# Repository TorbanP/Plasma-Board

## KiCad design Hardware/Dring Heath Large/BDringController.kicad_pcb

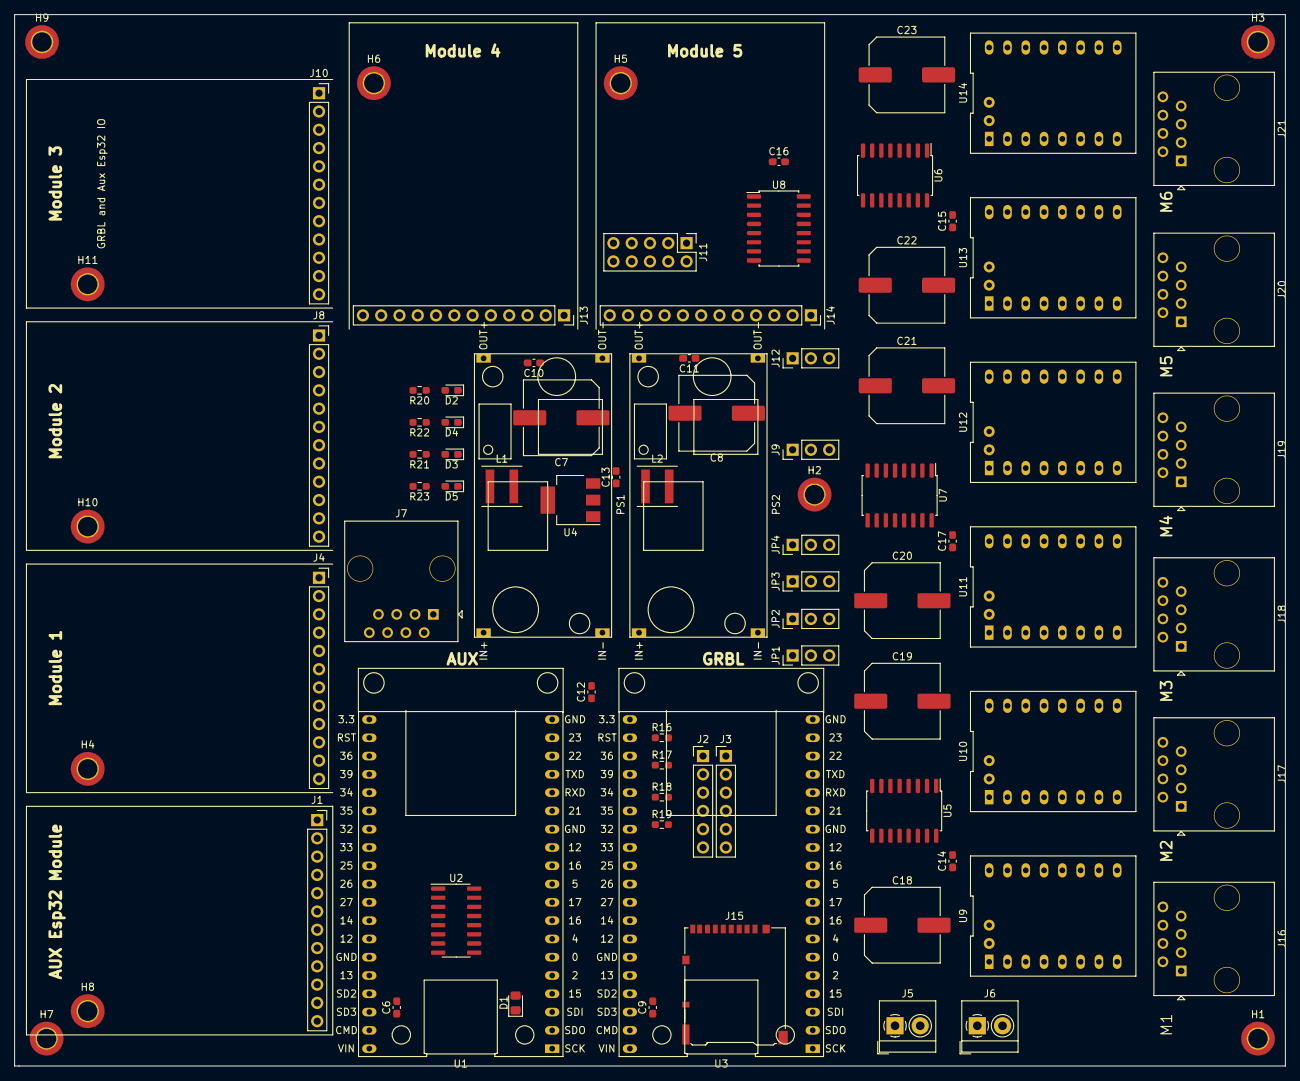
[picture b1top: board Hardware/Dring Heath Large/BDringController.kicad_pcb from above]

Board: 2 copper layers, 176.5 x 146.1 mm, 85 parts (0 on the bottom side), 127 nets, no tracks yet.

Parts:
C6, C9, C10, C11, C14, C15, C16, C17: 100nf; C_0603_1608Metric_Pad1.08x0.95mm_HandSolder
C7, C8, C18, C19, C20, C21, C22, C23: 330uf; C_Elec_10x10.2
C12, C13: 10uf; C_0603_1608Metric_Pad1.08x0.95mm_HandSolder
D1: B340A; D_0805_2012Metric_Pad1.15x1.40mm_HandSolder
D2: Vdrive; D_0603_1608Metric_Pad1.05x0.95mm_HandSolder
D3: 5v; D_0603_1608Metric_Pad1.05x0.95mm_HandSolder
D4: 15v; D_0603_1608Metric_Pad1.05x0.95mm_HandSolder
D5: 3.3v; D_0603_1608Metric_Pad1.05x0.95mm_HandSolder
H1, H2, H3, H4, H5, H6, H7, H8, H9, H10, H11: MountingHole_2.7mm_M2.5_DIN965_Pad_TopBottom
J1, J4: Module 1; PinSocket_1x12_P2.54mm_Vertical
J2: Jumper; PinHeader_1x06_P2.54mm_Vertical
J3: Motor; PinHeader_1x06_P2.54mm_Vertical
J5: Ext Mot Drv; TerminalBlock_4Ucon_1x02_P3.50mm_Horizontal
J6: 01x02; TerminalBlock_4Ucon_1x02_P3.50mm_Horizontal
J7: THC_Display; RJ45_OST_PJ012-8P8CX_Vertical
J8: Module 2; PinSocket_1x12_P2.54mm_Vertical
J9: VMot; PinHeader_1x03_P2.54mm_Vertical
J10: Module 3; PinSocket_1x12_P2.54mm_Vertical
J11: JTAG; PinHeader_2x05_P2.54mm_Vertical
J12: Shift Regs and Motor Drvs; PinHeader_1x03_P2.54mm_Vertical
J13: Module 4; PinSocket_1x12_P2.54mm_Vertical
J14: Module 5; PinSocket_1x12_P2.54mm_Vertical
J15: Micro_SD_Card; microSD_HC_Hirose_DM3AT-SF-PEJM5
J16, J17, J18, J19, J20, J21: RJ45; RJ45_OST_PJ012-8P8CX_Vertical
JP1, JP3, JP4: MS1; PinHeader_1x03_P2.54mm_Vertical
JP2: MS2; PinHeader_1x03_P2.54mm_Vertical
L1, L2: 22uh; L_Coilcraft_XAL5030
PS1, PS2: DC-DC_BuckAdg; Buck_Module
R16, R17, R18, R19: 10k; R_0603_1608Metric_Pad0.98x0.95mm_HandSolder
R20, R21, R22, R23: 1k; R_0603_1608Metric_Pad0.98x0.95mm_HandSolder
U1, U3: ESP32_38p
U2: 74LVC157A; SOP-16_3.9x9.9mm_P1.27mm
U4: TC1262-33; SOT-223
U5, U6, U7, U8: 74AHCT595; SO-16_5.3x10.2mm_P1.27mm
U9: X; ClearpathDriver
U10: Y; ClearpathDriver
U11: z; ClearpathDriver
U12: A; ClearpathDriver
U13: B; ClearpathDriver
U14: C; ClearpathDriver

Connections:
+3V3: C13.2, J7.1, J7.5, J11.1, J12.1, J15.4, R16.2, R17.2, R18.2, R19.2, R23.2, U2.16, U4.3
+5V: C7.1, C10.1, D1.2, J12.3, L1.2, R21.2, U4.1
+15V: C8.1, C11.1, J9.1, L2.2, R22.2
A_CS: U7.7, U12.4
A_Diag1: J3.3, U12.17
A_Dir: U7.5, U12.8
A_Enable: U7.4, U12.1
A_Limit: J2.3, J4.7, R18.1, U3.24
A_Step: U7.6, U12.7
B_CS: U6.3, U13.4
B_Diag1: J3.2, U13.17
B_Dir: U6.1, U13.8
B_Enable: U6.15, U13.1
B_Limit: J2.2, J8.6, R17.1, U3.23
B_Step: U6.2, U13.7
CS_SD: J15.2, U3.10
C_CS: U6.7, U14.4
C_Diag1: J3.1, U14.17
C_Dir: U6.5, U14.8
C_Enable: U6.4, U14.1
C_Limit: J2.1, J8.7, R16.1, U3.22
C_Step: U6.6, U14.7
EN: C6.2, C7.2, C8.2, C9.1, C10.2, C11.2, C12.2, C13.1, C14.1, C15.1, C16.1, C17.1, C18.2, C19.2, C20.2, C21.2, C22.2, C23.2, D2.1, D3.1, D4.1, D5.1, H1.1, H2.1, H3.1, H4.1, H5.1, H6.1, H7.1, H8.1, H9.1, H10.1, H11.1, J1.1, J1.12, J4.1, J4.12, J5.2, J7.2, J7.8, J8.1, J8.12, J10.1, J10.12, J11.3, J11.5, J11.9, J11.10, J13.1, J13.12, J14.1, J14.12, J15.6, J15.9, JP4.1, PS1.4, PS2.4, U1.13, U1.19, U1.33, U2.8, U2.15, U3.13, U3.19, U3.33, U4.2, U5.8, U5.13, U6.8, U6.13, U7.8, U7.13, U8.8, U8.13, U9.9, U9.15, U10.9, U10.15, U11.9, U11.15, U12.9, U12.15, U13.9, U13.15, U14.9, U14.15
GPIO2: J8.4, U3.5
GPIO04: J10.5, U3.7
GPIO12: J4.11, J8.11, J11.8, J13.7, J13.11, J14.11, U3.32
GPIO13: J4.9, J8.9, J11.4, J13.5, J13.9, J14.9, U3.34
GPIO14: J4.8, J8.8, J11.2, J13.4, J13.8, J14.8, U3.31
GPIO15: J4.10, J8.10, J11.6, J13.6, J13.10, J14.10, U3.4
GPIO16: J10.6, U3.8
GPIO25: J8.5, U3.28
GPIO26: J10.4, U3.29
GPIO27: J10.7, U3.30
GrbZDir: U2.5, U7.1
GrbZEn: U2.2, U7.15
GrbZStep: U2.11, U7.2
I2SO_24: J14.4, U8.15
I2SO_25: J14.6, U8.2
I2SO_26: J14.5, U8.1
I2SO_27: J14.7, U8.3
I2S_BCK: U3.17, U5.11, U6.11, U7.11, U8.11
I2S_DATA: U3.14, U5.14
I2S_WS: U3.9, U5.12, U6.12, U7.12, U8.12
MISO: J15.7, JP3.1, U3.12
MOSI: J15.3, JP1.1, U3.18
MS1: JP1.2, U9.2, U10.2, U11.2, U12.2, U13.2, U14.2
MS2: JP2.2, U9.3, U10.3, U11.3, U12.3, U13.3, U14.3
unnamed: C12.1, U3.21
unnamed: D2.2, R20.1
unnamed: D3.2, R21.1
unnamed: D4.2, R22.1
unnamed: D5.2, R23.1
unnamed: J1.4, U1.27
unnamed: J1.5, U1.28
unnamed: J1.6, U1.29
unnamed: J1.7, U1.30
unnamed: J1.8, U1.31
unnamed: J1.9, U1.34
unnamed: J1.10, U1.4
unnamed: J1.11, U1.32
unnamed: J5.1, J9.3
unnamed: J6.1, PS1.1, PS2.1
unnamed: J6.2, PS1.2, PS2.2
unnamed: J7.3, U1.16
unnamed: J7.4, U1.15
unnamed: J7.6, U1.8
unnamed: J16.2, U9.14
unnamed: J16.4, U9.13
unnamed: J16.6, U9.12
unnamed: J16.8, U9.11
unnamed: J17.2, U10.14
unnamed: J17.4, U10.13
unnamed: J17.6, U10.12
unnamed: J17.8, U10.11
unnamed: J18.2, U11.14
unnamed: J18.4, U11.13
unnamed: J18.6, U11.12
unnamed: J18.8, U11.11
unnamed: J19.2, U12.14
unnamed: J19.4, U12.13
unnamed: J19.6, U12.12
unnamed: J19.8, U12.11
unnamed: J20.2, U13.14
unnamed: J20.4, U13.13
unnamed: J20.6, U13.12
unnamed: J20.8, U13.11
unnamed: J21.2, U14.14
unnamed: J21.4, U14.13
unnamed: J21.6, U14.12
unnamed: J21.8, U14.11
unnamed: L1.1, PS1.3
unnamed: L2.1, PS2.3
unnamed: U1.11, U2.6
unnamed: U1.12, U2.3
unnamed: U1.18, U2.10
unnamed: U5.9, U7.14
unnamed: U6.9, U8.14
unnamed: U6.14, U7.9
SCK: J15.5, JP2.1, U3.11
Step_R: JP3.2, U9.5, U10.5, U11.5, U12.5, U13.5, U14.5
Step_S: JP4.2, U9.6, U10.6, U11.6, U12.6, U13.6, U14.6
TCHIO17: J10.10, U1.9
TCHIO21: J10.9, U1.14
TCHIO22: J10.8, U1.17
TCHIO35: U1.25, U11.18, U12.18
TorchTrigger: J10.11, U1.26, U2.1
VCC: C14.2, C15.2, C16.2, C17.2, C18.1, C19.1, C20.1, C21.1, C22.1, C23.1, J1.3, J4.3, J8.3, J10.3, J12.2, J13.3, J14.3, JP1.3, JP2.3, JP3.3, JP4.3, U5.10, U5.16, U6.10, U6.16, U7.10, U7.16, U8.10, U8.16, U9.10, U10.10, U11.10, U12.10, U13.10, U14.10
Vdrive: J1.2, J4.2, J8.2, J9.2, J10.2, J13.2, J14.2, J16.1, J16.3, J16.5, J16.7, J17.1, J17.3, J17.5, J17.7, J18.1, J18.3, J18.5, J18.7, J19.1, J19.3, J19.5, J19.7, J20.1, J20.3, J20.5, J20.7, J21.1, J21.3, J21.5, J21.7, R20.2, U9.16, U10.16, U11.16, U12.16, U13.16, U14.16
Vin: C6.1, C9.2, D1.1, U1.38, U3.38
X_CS: U5.3, U9.4
X_Diag1: J3.6, U9.17
X_Dir: U5.1, U9.8
X_Enable: U5.15, U9.1
X_Limit: J2.6, J4.4, U3.27
X_Step: U5.2, U9.7
Y_CS: U5.7, U10.4
Y_Diag1: J3.5, U10.17
Y_Dir: U5.5, U10.8
Y_Enable: U5.4, U10.1
Y_Limit: J2.5, J4.5, U3.26
Y_Step: U5.6, U10.7
Z_CS: U7.3, U11.4
Z_Diag1: J3.4, U11.17
Z_Dir: U2.7, U11.8
Z_Enable: U2.4, U11.1
Z_Limit: J2.4, J4.6, R19.1, U3.25
Z_Steo: U2.9, U11.7

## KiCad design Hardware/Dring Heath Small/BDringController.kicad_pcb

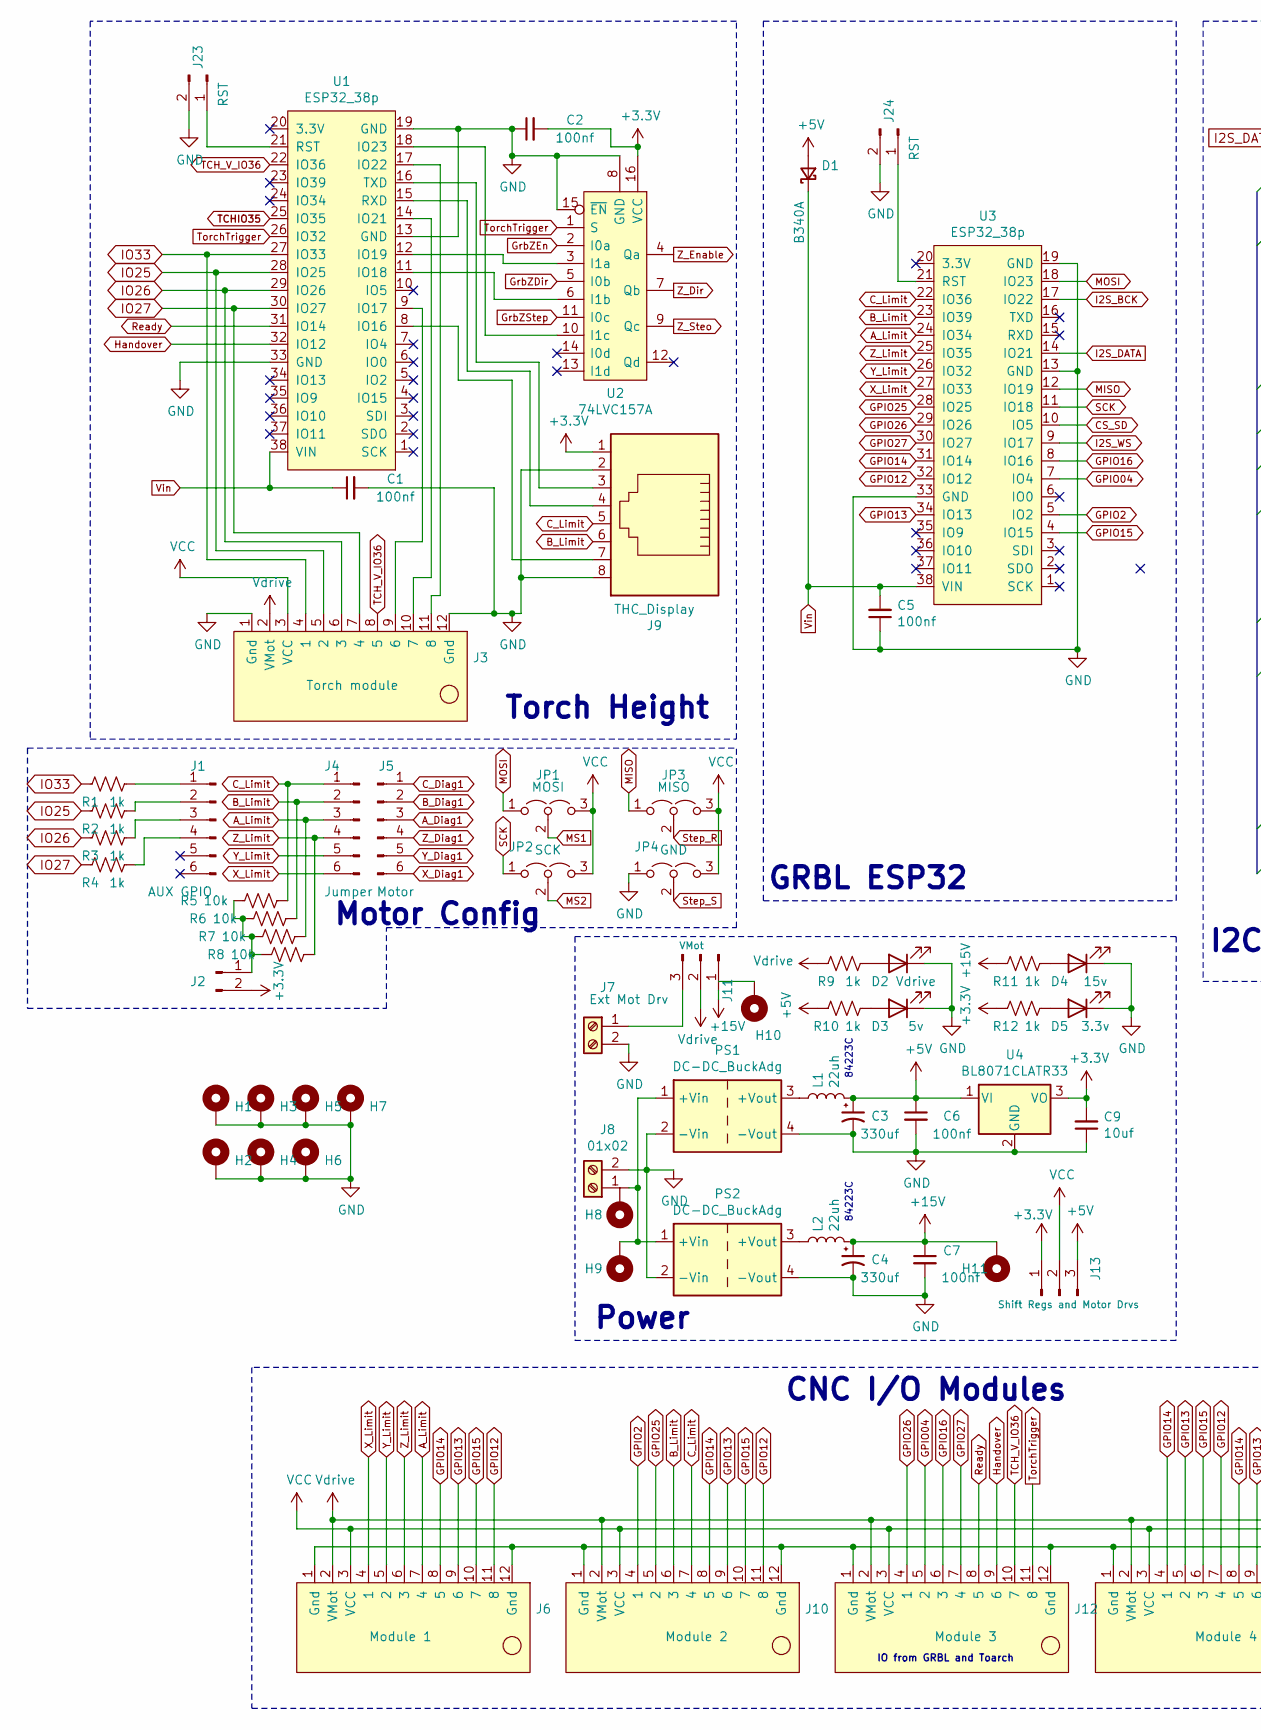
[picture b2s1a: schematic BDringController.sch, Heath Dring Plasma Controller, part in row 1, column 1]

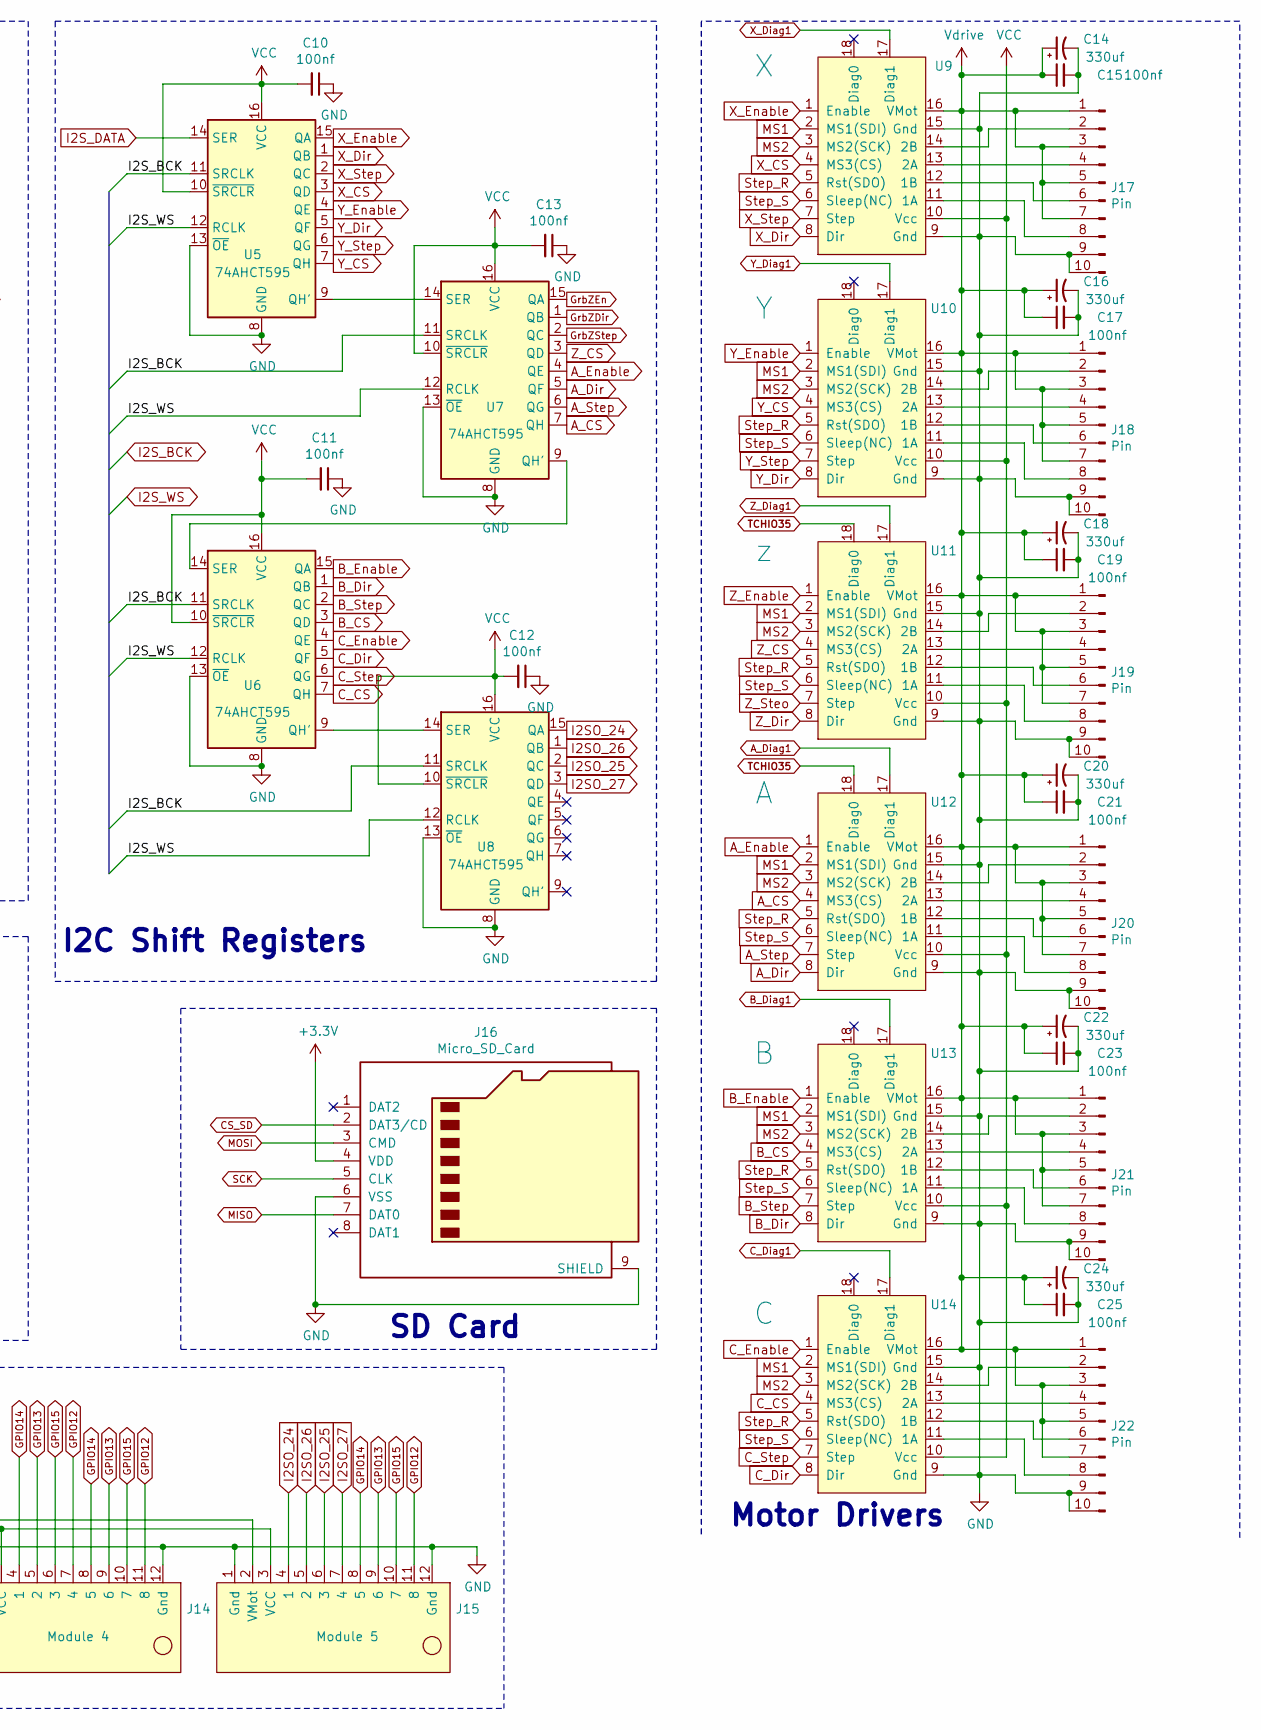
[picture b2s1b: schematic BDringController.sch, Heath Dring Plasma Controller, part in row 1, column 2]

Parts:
C1, C2, C5, C6, C7, C10, C11, C12, C13, C15, C17, C19, C21, C23, C25: 100nf; C_0603_1608Metric_Pad1.08x0.95mm_HandSolder
C3, C4, C14, C16, C18, C20, C22, C24: 330uf; CP_Elec_10x12.6
C9: 10uf; C_0603_1608Metric_Pad1.08x0.95mm_HandSolder
D1: B340A; D_0805_2012Metric_Pad1.15x1.40mm_HandSolder
D2: Vdrive; D_0603_1608Metric_Pad1.05x0.95mm_HandSolder
D3: 5v; D_0603_1608Metric_Pad1.05x0.95mm_HandSolder
D4: 15v; D_0603_1608Metric_Pad1.05x0.95mm_HandSolder
D5: 3.3v; D_0603_1608Metric_Pad1.05x0.95mm_HandSolder
H1, H2, H3, H4, H5, H6, H7: MountingHole_2.7mm_M2.5_DIN965_Pad_TopBottom
H8, H9, H10, H11: Pin_D0.9mm_L10.0mm_W2.4mm_FlatFork
J1: AUX GPIO; PinHeader_1x06_P2.54mm_Vertical
J2: PinHeader_1x02_P2.54mm_Vertical
J3: Torch module; PinSocket_1x12_P2.54mm_Vertical
J4: Jumper; PinHeader_1x06_P2.54mm_Vertical
J5: Motor; PinHeader_1x06_P2.54mm_Vertical
J6: Module 1; PinSocket_1x12_P2.54mm_Vertical
J7: Ext Mot Drv; TerminalBlock_4Ucon_1x02_P3.50mm_Horizontal
J8: 01x02; TerminalBlock_4Ucon_1x02_P3.50mm_Horizontal
J9: THC_Display; RJ45_BEL_SS74301-00x_Vertical
J10: Module 2; PinSocket_1x12_P2.54mm_Vertical
J11: VMot; PinHeader_1x03_P2.54mm_Vertical
J12: Module 3; PinSocket_1x12_P2.54mm_Vertical
J13: Shift Regs and Motor Drvs; PinHeader_1x03_P2.54mm_Vertical
J14: Module 4; PinSocket_1x12_P2.54mm_Vertical
J15: Module 5; PinSocket_1x12_P2.54mm_Vertical
J16: Micro_SD_Card; microSD_HC_Hirose_DM3AT-SF-PEJM5
J17, J18, J19, J20, J21, J22: Pin; PinHeader_2x05_P2.54mm_Vertical
J23, J24: RST; PinHeader_1x02_P2.54mm_Vertical
JP1: MOSI; PinHeader_1x03_P2.54mm_Vertical
JP2: SCK; PinHeader_1x03_P2.54mm_Vertical
JP3: MISO; PinHeader_1x03_P2.54mm_Vertical
JP4: GND; PinHeader_1x03_P2.54mm_Vertical
L1, L2: 22uh; L_Coilcraft_XAL5030
PS1, PS2: DC-DC_BuckAdg; Buck_Module
R1, R2, R3, R4, R9, R10, R11, R12: 1k; R_0603_1608Metric_Pad0.98x0.95mm_HandSolder
R5, R6, R7, R8: 10k; R_0603_1608Metric_Pad0.98x0.95mm_HandSolder
U1, U3: ESP32_38p
U2: 74LVC157A; SOP-16_3.9x9.9mm_P1.27mm
U4: BL8071CLATR33; SOT-223
U5, U6, U7, U8: 74AHCT595; SO-16_5.3x10.2mm_P1.27mm
U9: X; ClearpathDriver
U10: Y; ClearpathDriver
U11: z; ClearpathDriver
U12: A; ClearpathDriver
U13: B; ClearpathDriver
U14: C; ClearpathDriver

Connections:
+3V3: C2.2, C9.2, J2.2, J9.1, J13.1, J16.4 (VDD), R12.2, U2.16 (VCC), U4.3 (VO)
+5V: C3.1, C6.1, D1.2 (A), J13.3, L1.2, R10.2, U4.1 (VI)
+15V: C4.1, C7.1, H11.1, J11.1, L2.2, R11.2
A_CS: U7.7 (QH), U12.4 (MS3(CS))
A_Diag1: J5.3, U12.17 (Diag1)
A_Dir: U7.5 (QF), U12.8 (Dir)
A_Enable: U7.4 (QE), U12.1 (Enable)
A_Limit: J4.3, J6.7 (4), R7.1, U3.24 (IO34)
A_Step: U7.6 (QG), U12.7 (Step)
B_CS: U6.3 (QD), U13.4 (MS3(CS))
B_Diag1: J5.2, U13.17 (Diag1)
B_Dir: U6.1 (QB), U13.8 (Dir)
B_Enable: U6.15 (QA), U13.1 (Enable)
B_Limit: J4.2, J9.6, J10.6 (3), R6.1, U3.23 (IO39)
B_Step: U6.2 (QC), U13.7 (Step)
CS_SD: J16.2 (DAT3/CD), U3.10 (IO5)
C_CS: U6.7 (QH), U14.4 (MS3(CS))
C_Diag1: J5.1, U14.17 (Diag1)
C_Dir: U6.5 (QF), U14.8 (Dir)
C_Enable: U6.4 (QE), U14.1 (Enable)
C_Limit: J4.1, J9.5, J10.7 (4), R5.1, U3.22 (IO36)
C_Step: U6.6 (QG), U14.7 (Step)
GND: C1.2, C2.1, C3.2, C4.2, C5.1, C6.2, C7.2, C9.1, C10.1, C11.1, C12.1, C13.1, C14.2, C15.2, C16.2, C17.2, C18.2, C19.2, C20.2, C21.2, C22.2, C23.2, C24.2, C25.2, D2.1 (K), D3.1 (K), D4.1 (K), D5.1 (K), H1.1, H2.1, H3.1, H4.1, H5.1, H6.1, H7.1, J3.1 (Gnd), J3.12 (Gnd), J6.1 (Gnd), J6.12 (Gnd), J7.2, J8.2, J9.2, J9.8, J10.1 (Gnd), J10.12 (Gnd), J12.1 (Gnd), J12.12 (Gnd), J14.1 (Gnd), J14.12 (Gnd), J15.1 (Gnd), J15.12 (Gnd), J16.6 (VSS), J16.9 (SHIELD), J17.9, J17.10, J18.9, J18.10, J19.9, J19.10, J20.9, J20.10, J21.9, J21.10, J22.9, J22.10, J23.2, J24.2, JP4.1 (A), PS1.2 (-Vin), PS1.4 (-Vout), PS2.2 (-Vin), PS2.4 (-Vout), U1.13 (GND), U1.19 (GND), U1.33 (GND), U2.8 (GND), U2.15 (~EN), U3.13 (GND), U3.19 (GND), U3.33 (GND), U4.2 (GND), U5.8 (GND), U5.13 (~OE), U6.8 (GND), U6.13 (~OE), U7.8 (GND), U7.13 (~OE), U8.8 (GND), U8.13 (~OE), U9.9 (Gnd), U9.15 (Gnd), U10.9 (Gnd), U10.15 (Gnd), U11.9 (Gnd), U11.15 (Gnd), U12.9 (Gnd), U12.15 (Gnd), U13.9 (Gnd), U13.15 (Gnd), U14.9 (Gnd), U14.15 (Gnd)
GPIO2: J10.4 (1), U3.5 (IO2)
GPIO04: J12.5 (2), U3.7 (IO4)
GPIO12: J6.11 (8), J10.11 (8), J14.7 (4), J14.11 (8), J15.11 (8), U3.32 (IO12)
GPIO13: J6.9 (6), J10.9 (6), J14.5 (2), J14.9 (6), J15.9 (6), U3.34 (IO13)
GPIO14: J6.8 (5), J10.8 (5), J14.4 (1), J14.8 (5), J15.8 (5), U3.31 (IO14)
GPIO15: J6.10 (7), J10.10 (7), J14.6 (3), J14.10 (7), J15.10 (7), U3.4 (IO15)
GPIO16: J12.6 (3), U3.8 (IO16)
GPIO25: J10.5 (2), U3.28 (IO25)
GPIO26: J12.4 (1), U3.29 (IO26)
GPIO27: J12.7 (4), U3.30 (IO27)
GrbZDir: U2.5 (I0b), U7.1 (QB)
GrbZEn: U2.2 (I0a), U7.15 (QA)
GrbZStep: U2.11 (I0c), U7.2 (QC)
Handover: J12.9 (6), U1.32 (IO12)
I2SO_24: J15.4 (1), U8.15 (QA)
I2SO_25: J15.6 (3), U8.2 (QC)
I2SO_26: J15.5 (2), U8.1 (QB)
I2SO_27: J15.7 (4), U8.3 (QD)
I2S_BCK: U3.17 (IO22), U5.11 (SRCLK), U6.11 (SRCLK), U7.11 (SRCLK), U8.11 (SRCLK)
I2S_DATA: U3.14 (IO21), U5.14 (SER)
I2S_WS: U3.9 (IO17), U5.12 (RCLK), U6.12 (RCLK), U7.12 (RCLK), U8.12 (RCLK)
IO25: J3.5 (2), R2.2, U1.28 (IO25)
IO26: J3.6 (3), R3.2, U1.29 (IO26)
IO27: J3.7 (4), R4.2, U1.30 (IO27)
IO33: J3.4 (1), R1.2, U1.27 (IO33)
MISO: J16.7 (DAT0), JP3.1 (A), U3.12 (IO19)
MOSI: J16.3 (CMD), JP1.1 (A), U3.18 (IO23)
MS1: JP1.2 (C), U9.2 (MS1(SDI)), U10.2 (MS1(SDI)), U11.2 (MS1(SDI)), U12.2 (MS1(SDI)), U13.2 (MS1(SDI)), U14.2 (MS1(SDI))
MS2: JP2.2 (C), U9.3 (MS2(SCK)), U10.3 (MS2(SCK)), U11.3 (MS2(SCK)), U12.3 (MS2(SCK)), U13.3 (MS2(SCK)), U14.3 (MS2(SCK))
unnamed: D2.2 (A), R9.1
unnamed: D3.2 (A), R10.1
unnamed: D4.2 (A), R11.1
unnamed: D5.2 (A), R12.1
unnamed: H9.1, J8.1, PS1.1 (+Vin), PS2.1 (+Vin)
unnamed: J1.1, R1.1
unnamed: J1.2, R2.1
unnamed: J1.3, R3.1
unnamed: J1.4, R4.1
unnamed: J2.1, R5.2, R6.2, R7.2, R8.2
unnamed: J3.9 (6), U1.9 (IO17)
unnamed: J3.10 (7), U1.14 (IO21)
unnamed: J3.11 (8), U1.17 (IO22)
unnamed: J9.3, U1.16 (TXD)
unnamed: J9.4, U1.15 (RXD)
unnamed: J9.7, U1.8 (IO16)
unnamed: J7.1, J11.3
unnamed: J17.2, U9.14 (2B)
unnamed: J17.4, U9.13 (2A)
unnamed: J17.6, U9.12 (1B)
unnamed: J17.8, U9.11 (1A)
unnamed: J18.2, U10.14 (2B)
unnamed: J18.4, U10.13 (2A)
unnamed: J18.6, U10.12 (1B)
unnamed: J18.8, U10.11 (1A)
unnamed: J19.2, U11.14 (2B)
unnamed: J19.4, U11.13 (2A)
unnamed: J19.6, U11.12 (1B)
unnamed: J19.8, U11.11 (1A)
unnamed: J20.2, U12.14 (2B)
unnamed: J20.4, U12.13 (2A)
unnamed: J20.6, U12.12 (1B)
unnamed: J20.8, U12.11 (1A)
unnamed: J21.2, U13.14 (2B)
unnamed: J21.4, U13.13 (2A)
unnamed: J21.6, U13.12 (1B)
unnamed: J21.8, U13.11 (1A)
unnamed: J22.2, U14.14 (2B)
unnamed: J22.4, U14.13 (2A)
unnamed: J22.6, U14.12 (1B)
unnamed: J22.8, U14.11 (1A)
unnamed: J23.1, U1.21 (RST)
unnamed: J24.1, U3.21 (RST)
unnamed: L1.1, PS1.3 (+Vout)
unnamed: L2.1, PS2.3 (+Vout)
unnamed: U1.11 (IO18), U2.6 (I1b)
unnamed: U1.12 (IO19), U2.3 (I1a)
unnamed: U1.18 (IO23), U2.10 (I1c)
unnamed: U5.9 (QH'), U7.14 (SER)
unnamed: U6.9 (QH'), U8.14 (SER)
unnamed: U6.14 (SER), U7.9 (QH')
Ready: J12.8 (5), U1.31 (IO14)
SCK: J16.5 (CLK), JP2.1 (A), U3.11 (IO18)
Step_R: JP3.2 (C), U9.5 (Rst(SDO)), U10.5 (Rst(SDO)), U11.5 (Rst(SDO)), U12.5 (Rst(SDO)), U13.5 (Rst(SDO)), U14.5 (Rst(SDO))
Step_S: JP4.2 (C), U9.6 (Sleep(NC)), U10.6 (Sleep(NC)), U11.6 (Sleep(NC)), U12.6 (Sleep(NC)), U13.6 (Sleep(NC)), U14.6 (Sleep(NC))
TCHIO35: U1.25 (IO35), U11.18 (Diag0), U12.18 (Diag0)
TCH_V_IO36: J3.8 (5), J12.10 (7), U1.22 (IO36)
TorchTrigger: J12.11 (8), U1.26 (IO32), U2.1 (S)
VCC: C10.2, C11.2, C12.2, C13.2, J3.3 (VCC), J6.3 (VCC), J10.3 (VCC), J12.3 (VCC), J13.2, J14.3 (VCC), J15.3 (VCC), JP1.3 (B), JP2.3 (B), JP3.3 (B), JP4.3 (B), U5.10 (~SRCLR), U5.16 (VCC), U6.10 (~SRCLR), U6.16 (VCC), U7.10 (~SRCLR), U7.16 (VCC), U8.10 (~SRCLR), U8.16 (VCC), U9.10 (Vcc), U10.10 (Vcc), U11.10 (Vcc), U12.10 (Vcc), U13.10 (Vcc), U14.10 (Vcc)
Vdrive: C14.1, C15.1, C16.1, C17.1, C18.1, C19.1, C20.1, C21.1, C22.1, C23.1, C24.1, C25.1, J3.2 (VMot), J6.2 (VMot), J10.2 (VMot), J11.2, J12.2 (VMot), J14.2 (VMot), J15.2 (VMot), J17.1, J17.3, J17.5, J17.7, J18.1, J18.3, J18.5, J18.7, J19.1, J19.3, J19.5, J19.7, J20.1, J20.3, J20.5, J20.7, J21.1, J21.3, J21.5, J21.7, J22.1, J22.3, J22.5, J22.7, R9.2, U9.16 (VMot), U10.16 (VMot), U11.16 (VMot), U12.16 (VMot), U13.16 (VMot), U14.16 (VMot)
Vin: C1.1, C5.2, D1.1 (K), U1.38 (VIN), U3.38 (VIN)
X_CS: U5.3 (QD), U9.4 (MS3(CS))
X_Diag1: J5.6, U9.17 (Diag1)
X_Dir: U5.1 (QB), U9.8 (Dir)
X_Enable: U5.15 (QA), U9.1 (Enable)
X_Limit: J4.6, J6.4 (1), U3.27 (IO33)
X_Step: U5.2 (QC), U9.7 (Step)
Y_CS: U5.7 (QH), U10.4 (MS3(CS))
Y_Diag1: J5.5, U10.17 (Diag1)
Y_Dir: U5.5 (QF), U10.8 (Dir)
Y_Enable: U5.4 (QE), U10.1 (Enable)
Y_Limit: J4.5, J6.5 (2), U3.26 (IO32)
Y_Step: U5.6 (QG), U10.7 (Step)
Z_CS: U7.3 (QD), U11.4 (MS3(CS))
Z_Diag1: J5.4, U11.17 (Diag1)
Z_Dir: U2.7 (Qb), U11.8 (Dir)
Z_Enable: U2.4 (Qa), U11.1 (Enable)
Z_Limit: J4.4, J6.6 (3), R8.1, U3.25 (IO35)
Z_Steo: U2.9 (Qc), U11.7 (Step)

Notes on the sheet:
I2C Shift Registers
Motor Drivers
CNC I/O Modules
SD Card
GRBL ESP32
84223C
Torch Height
Power
Motor Config
IO from GRBL and Toarch

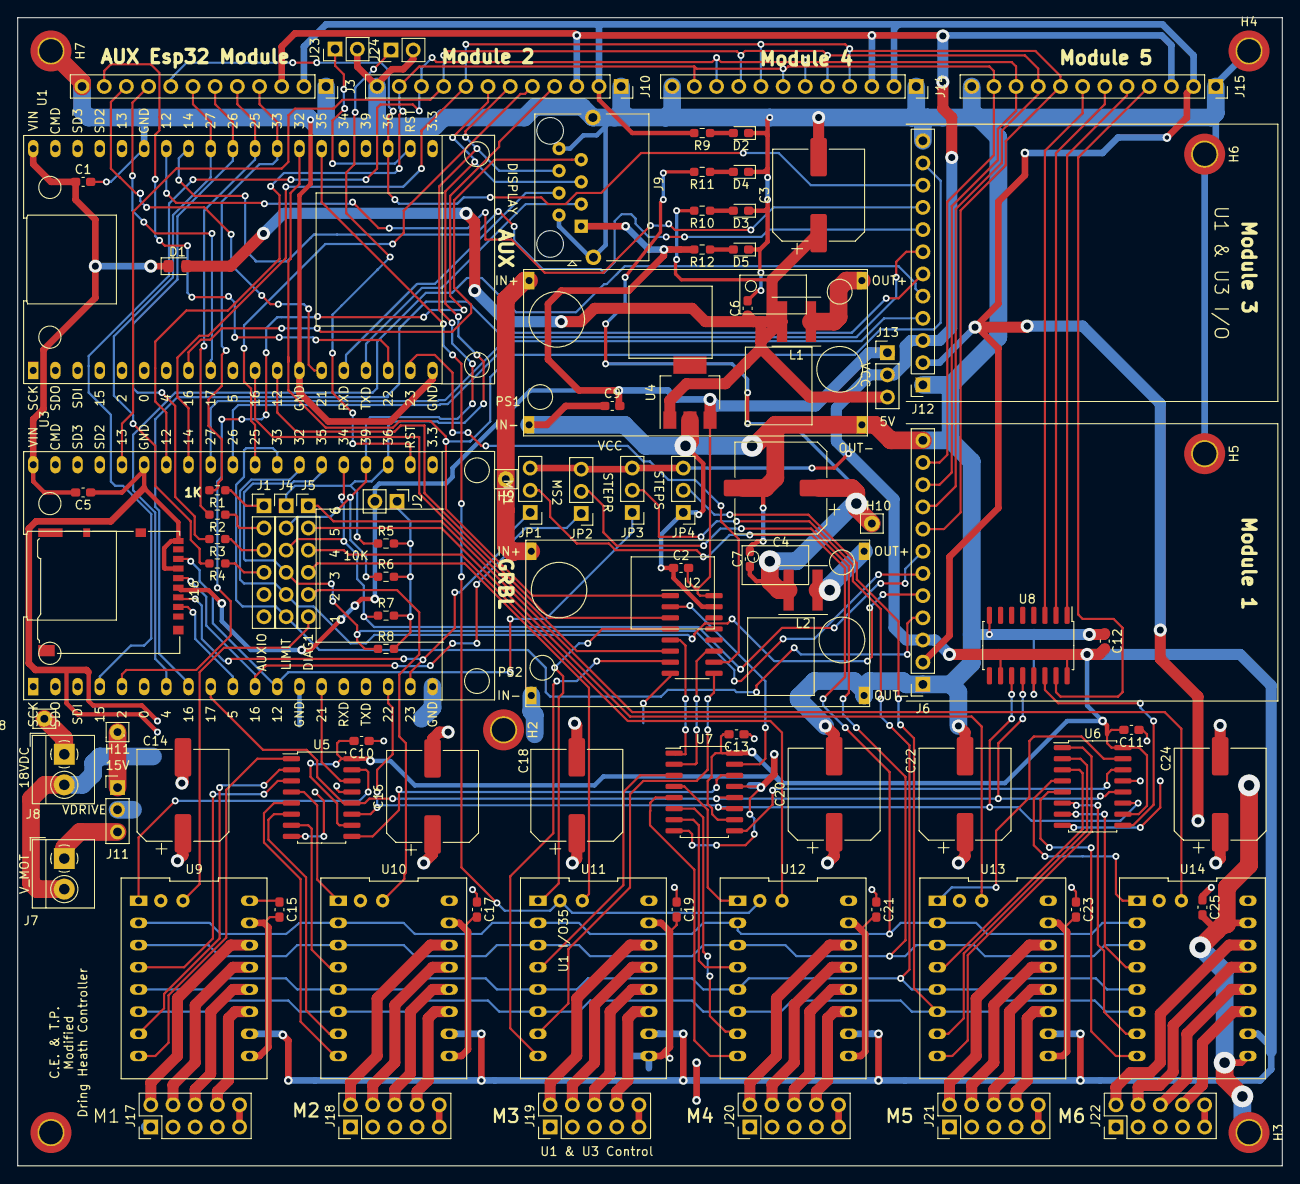
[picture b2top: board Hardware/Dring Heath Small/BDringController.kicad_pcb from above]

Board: 2 copper layers, 144.8 x 131.4 mm, 98 parts (0 on the bottom side), 131 nets.

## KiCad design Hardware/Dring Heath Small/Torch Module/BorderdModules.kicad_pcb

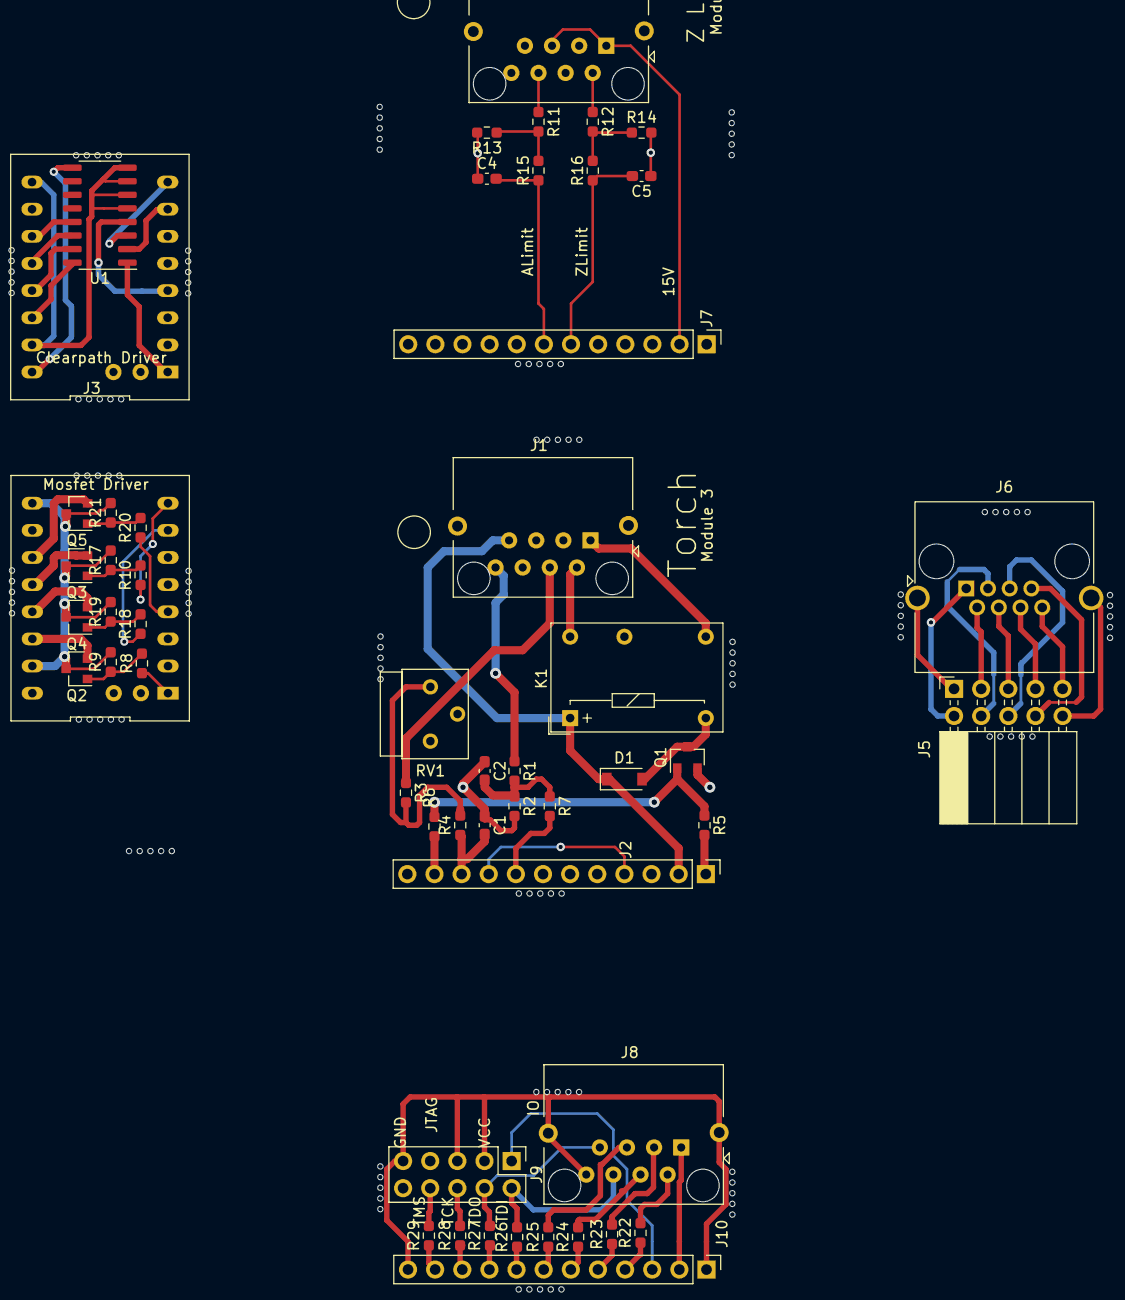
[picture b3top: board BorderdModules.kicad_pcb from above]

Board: 2 copper layers, 52 parts (0 on the bottom side), 66 nets.

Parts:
C1: 22nf; C_0603_1608Metric_Pad1.08x0.95mm_HandSolder
C2, C4, C5: 1uf; C_0603_1608Metric_Pad1.08x0.95mm_HandSolder
D1: D; D_SOD-123
J1, J8: Torch; RJ45_Torb_Vertical
J2: Module3; PinHeader_1x12_P2.54mm_Vertical
J3: Conn_01x18_Male; ClearpathDriver
J4: Limit; RJ45_Torb_Vertical
J5: PinSocket_2x05_P2.54mm_Horizontal
J6: Motor; RJ45_Amphenol_RJHSE5380
J7: Module1; PinHeader_1x12_P2.54mm_Vertical
J9: 2.54 pin; PinHeader_2x05_P2.54mm_Vertical
J10: Module conn; PinHeader_1x12_P2.54mm_Vertical
K1: G6E; Relay_SPDT_Omron_G6E
Q1, Q2, Q3, Q4, Q5: IRLML2402; SOT-23
R1: 3.3K; R_0603_1608Metric_Pad0.98x0.95mm_HandSolder
R2, R3, R13, R14: 1k; R_0603_1608Metric_Pad0.98x0.95mm_HandSolder
R4, R5, R7, R9, R15, R16, R17, R19, R21: 10k; R_0603_1608Metric_Pad0.98x0.95mm_HandSolder
R6, R8, R10, R18, R20, R22, R23, R24, R25, R26, R27, R28, R29: 200; R_0603_1608Metric_Pad0.98x0.95mm_HandSolder
R11, R12: 3.3k; R_0603_1608Metric_Pad0.98x0.95mm_HandSolder
RV1: 2K; Potentiometer_Bourns_3339S_Horizontal
U1: ULN2002; SO-16_3.9x9.9mm_P1.27mm

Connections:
unnamed: C1.1, C2.1, J1.3, J1.9, J1.10, J2.1, J2.12, Q1.2, R2.2, R5.2, RV1.1, RV1.2
unnamed: C1.2, J2.10, R4.1
unnamed: C2.2, R1.2, R2.1, R7.1
unnamed: C4.1, C5.1, J4.9, J4.10, J7.1, J7.12, R13.2, R14.2
unnamed: C4.2, J7.7, R15.1
unnamed: C5.2, J7.6, R16.1
unnamed: D1.1, J1.7, J2.2, K1.1
unnamed: D1.2, K1.6, Q1.3
unnamed: J1.1, K1.7
unnamed: J1.2, K1.12
unnamed: J1.4, R3.1
unnamed: J1.8, R1.1
unnamed: J2.4, J2.9
unnamed: J2.8, R7.2
unnamed: J2.11, R6.1
unnamed: J3.1, U1.1
unnamed: J3.4, U1.4
unnamed: J3.7, U1.2
unnamed: J3.8, U1.3
unnamed: J3.11, U1.13
unnamed: J3.12, U1.14
unnamed: J3.13, U1.15
unnamed: J3.14, U1.16
unnamed: J3.9, J3.15, U1.5, U1.6, U1.7, U1.8
unnamed: J3.16, U1.9
unnamed: J4.1, J4.5, J7.2
unnamed: J4.2, R12.1
unnamed: J4.6, R11.1
unnamed: J5.1, J6.9
unnamed: J5.2, J6.1
unnamed: J5.3, J6.2
unnamed: J5.4, J6.3
unnamed: J5.5, J6.4
unnamed: J5.6, J6.5
unnamed: J5.7, J6.6
unnamed: J5.8, J6.7
unnamed: J5.9, J6.8
unnamed: J5.10, J6.10
unnamed: J8.2, R22.2
unnamed: J8.3, R23.2
unnamed: J8.4, R24.2
unnamed: J8.5, R25.2
unnamed: J8.6, J9.2, R26.2
unnamed: J8.7, J9.4, R27.2
unnamed: J9.6, R28.2
unnamed: J9.8, R29.2
unnamed: J8.8, J8.9, J8.10, J9.3, J9.5, J9.9, J10.1, J10.12
unnamed: J8.1, J10.2
unnamed: J9.1, J10.3
unnamed: J10.4, R22.1
unnamed: J10.5, R23.1
unnamed: J10.6, R24.1
unnamed: J10.7, R25.1
unnamed: J10.8, R26.1
unnamed: J10.9, R27.1
unnamed: J10.10, R28.1
unnamed: J10.11, R29.1
unnamed: Q2.3, Q3.3, Q4.3, Q5.3, R9.2, R17.2, R19.2, R21.2
unnamed: Q1.1, R5.1, R6.2
unnamed: Q2.1, R8.2, R9.1
unnamed: Q3.1, R10.2, R17.1
unnamed: Q4.1, R18.2, R19.1
unnamed: Q5.1, R20.2, R21.1
unnamed: R3.2, R4.2, RV1.3
unnamed: R11.2, R13.1, R15.2
unnamed: R12.2, R14.1, R16.2

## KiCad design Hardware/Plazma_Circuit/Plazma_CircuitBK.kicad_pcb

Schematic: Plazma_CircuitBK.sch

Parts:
C1, C3, C4, C5, C6, C7, C8, C9, C10, C11: .1uf; C_0603_1608Metric_Pad1.08x0.95mm_HandSolder
C2: 470uf; CP_Elec_6.3x5.8
D1, D2, D3, D4: 1N4001; D_0603_1608Metric_Pad1.05x0.95mm_HandSolder
J1: 18V AC IN; TerminalBlock_Altech_AK300-2_P5.00mm
J2: R Axis; RJ45_Amphenol_RJHSE5380
J3: 8P8C_Shielded; RJ45_Amphenol_RJHSE5380
J4: STOPS; RJ45_Amphenol_RJHSE5380
J5: V to FREQ; TerminalBlock_Altech_AK300-4_P5.00mm
J6: TORCH; RJ45_Amphenol_54602-x08_Horizontal
J7: SPARE; PinHeader_1x04_P2.00mm_Horizontal
J8: Z Axis; RJ45_Amphenol_RJHSE5380
J9: Y1Axis; RJ45_Amphenol_RJHSE5380
J10: Y2 Axis; RJ45_Amphenol_RJHSE5380
J11: X Axis; RJ45_Amphenol_RJHSE5380
K1: TOARCH FIRE; Relay_DPDT_Omron_G5V-2
PS1, PS2: DC-DC_BuckAdg; DC-DC_BuckADG
R1, R4, R7, R8, R13, R16, R19, R22, R25: 10k; R_0603_1608Metric_Pad0.98x0.95mm_HandSolder
R2, R5, R9, R11, R14, R17, R20, R23, R26: 3.3k; R_0603_1608Metric_Pad0.98x0.95mm_HandSolder
R3, R6, R10, R12, R15, R18, R21, R24, R27: 1k; R_0603_1608Metric_Pad0.98x0.95mm_HandSolder
U1, U4, U5: MC1413; SOIC-16_3.9x9.9mm_P1.27mm
U2: ESP32Master; ESP32DevKitV1
U3: ESP32 Torch; ESP32DevKitV1

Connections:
+3V3: J3.7, U2.1; also elsewhere on the board
+5V: PS2.3, U2.36, U3.36
+15V: J2.1, J2.3, J2.5, J2.7, J4.1, J4.3, J7.1, J7.3, J8.1, J8.3, J8.5, J8.7, J9.1, J9.3, J9.5, J9.7, J10.1, J10.3, J10.5, J10.7, J11.1, J11.3, J11.5, J11.7, K1.4, K1.13, K1.16, PS1.3, U1.9 (COM), U4.9 (COM), U5.9 (COM); also elsewhere on the board
/XDIR: J11.6, U5.12 (O5)
/XEN: J11.2, U5.14 (O3)
/XSP: J11.4, U5.13 (O4)
/XTQ: J11.8, R14.1
/Y1DIR: J9.4, U4.11 (O6)
/Y1EN: J9.2, U4.13 (O4)
/Y1SP: J9.6, U4.12 (O5)
/Y1TQ: J9.8, R23.1
/Y2DIR: J10.6, U5.15 (O2)
/Y2EN: J10.2, U4.10 (O7)
/Y2SP: J10.4, U5.16 (O1)
/Y2TQ: J10.8, R20.1
/ZDIR: J8.6, U4.14 (O3)
/ZEN: J8.2, U4.16 (O1)
/ZSP: J8.4, U4.15 (O2)
/ZTQ: J8.8, R9.1
CS: U2.6, U3.6
DISPCS: J3.4, U2.17; also elsewhere on the board
GND: C1.2, C2.2, C3.2, C4.2, C5.2, C6.2, C7.2, C8.2, C9.2, C10.2, C11.2, D3.2 (A), D4.2 (A), J2.SH, J3.8, J3.SH, J4.SH, J5.2, J5.4, J6.2, J6.4, J6.8, J6.SH, J8.SH, J9.SH, J10.SH, J11.SH, PS1.2, PS1.4, PS2.2, PS2.4, R3.2, R6.2, R10.2, R12.2, R15.2, R18.2, R21.2, R24.2, R27.2, U1.8 (GND), U2.35, U3.35, U4.8 (GND), U5.8 (GND); also elsewhere on the board
INRDIR: U1.3 (I3), U3.28
INREN: U1.1 (I1), U3.26
INRSP: U1.2 (I2), U3.27
INRTQ: C3.1, R1.2, U3.25
INTD: C6.1, R8.2, U3.22
INTH: J5.3, U3.24
INTHD: C4.1, R4.2, U3.23
INTM: C11.1, R25.2, U3.21
INXTQ: C7.1, R13.2, U2.20
INY1TQ: C10.1, R22.2, U2.22
INY2TQ: C9.1, R19.2, U2.21
INZTQ: C5.1, R7.2, U3.20
MISO: J3.2, U2.30, U3.30; also elsewhere on the board
MOSI: J3.3, U2.31, U3.31; also elsewhere on the board
unnamed: C1.1, C2.1, D1.1 (K), D2.1 (K), PS1.1, PS2.1
unnamed: D1.2 (A), D4.1 (K), J1.2
unnamed: D2.2 (A), D3.1 (K), J1.1
unnamed: J2.2, U1.16 (O1)
unnamed: J2.4, U1.15 (O2)
unnamed: J2.6, U1.14 (O3)
unnamed: J2.8, R2.1
unnamed 43: J3.5, U2.8; also elsewhere on the board
unnamed 44: J3.6, U2.7; also elsewhere on the board
unnamed: J4.2, R11.1
unnamed: J4.4, R5.1
unnamed: J5.1, J6.7
unnamed: J6.1, K1.8, K1.9
unnamed: J6.3, R26.1
unnamed: J7.2, R17.1
unnamed: J7.4, U5.10 (O7)
unnamed: K1.1, U5.11 (O6)
unnamed: R1.1, R2.2, R3.1
unnamed: R4.1, R5.2, R6.1
unnamed: R7.1, R9.2, R10.1
unnamed: R8.1, R11.2, R12.1
unnamed: R13.1, R14.2, R15.1
unnamed: R16.1, R17.2, R18.1
unnamed: R19.1, R20.2, R21.1
unnamed: R22.1, R23.2, R24.1
unnamed: R25.1, R26.2, R27.1
OTTS: U3.9, U5.6 (I6)
OTXDIR: U2.28, U5.5 (I5)
OTXEN: U2.26, U5.3 (I3)
OTXSP: U2.27, U5.4 (I4)
OTY1DIR: U2.12, U4.6 (I6)
OTY1EN: U2.9, U4.4 (I4)
OTY1SP: U2.10, U4.5 (I5)
OTY2DIR: U2.25, U5.2 (I2)
OTY2EN: U2.18, U4.7 (I7)
OTY2SP: U2.24, U5.1 (I1)
OTZDIR: U3.13, U4.3 (I3)
OTZEN: U3.10, U4.1 (I1)
OTZSP: U3.12, U4.2 (I2)
SLCK: J3.1, U2.29, U3.29; also elsewhere on the board
SPAREIN: C8.1, R16.2, U2.23
SPAREOUT: U2.14, U5.7 (I7)

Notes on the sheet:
VCC
R AXIS
PLASMA CONTROLLER
DEC 12 2020

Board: 4 copper layers, 63 parts (0 on the bottom side), 78 nets, no tracks yet.

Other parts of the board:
J3#2: DISPLAY; RJ45_Amphenol_54602-x08_Horizontal
K1#2: TOARCH TRIGGER; Relay_DPDT_Omron_G5V-2

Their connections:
+3V3: J3#2.7; also elsewhere on the board
+15V: K1#2.11; also elsewhere on the board
DISPCS: J3#2.4; also elsewhere on the board
GND: J3#2.8; also elsewhere on the board
MISO: J3#2.2; also elsewhere on the board
MOSI: J3#2.3; also elsewhere on the board
unnamed 43: J3#2.5; also elsewhere on the board
unnamed 44: J3#2.6; also elsewhere on the board
SLCK: J3#2.1; also elsewhere on the board
